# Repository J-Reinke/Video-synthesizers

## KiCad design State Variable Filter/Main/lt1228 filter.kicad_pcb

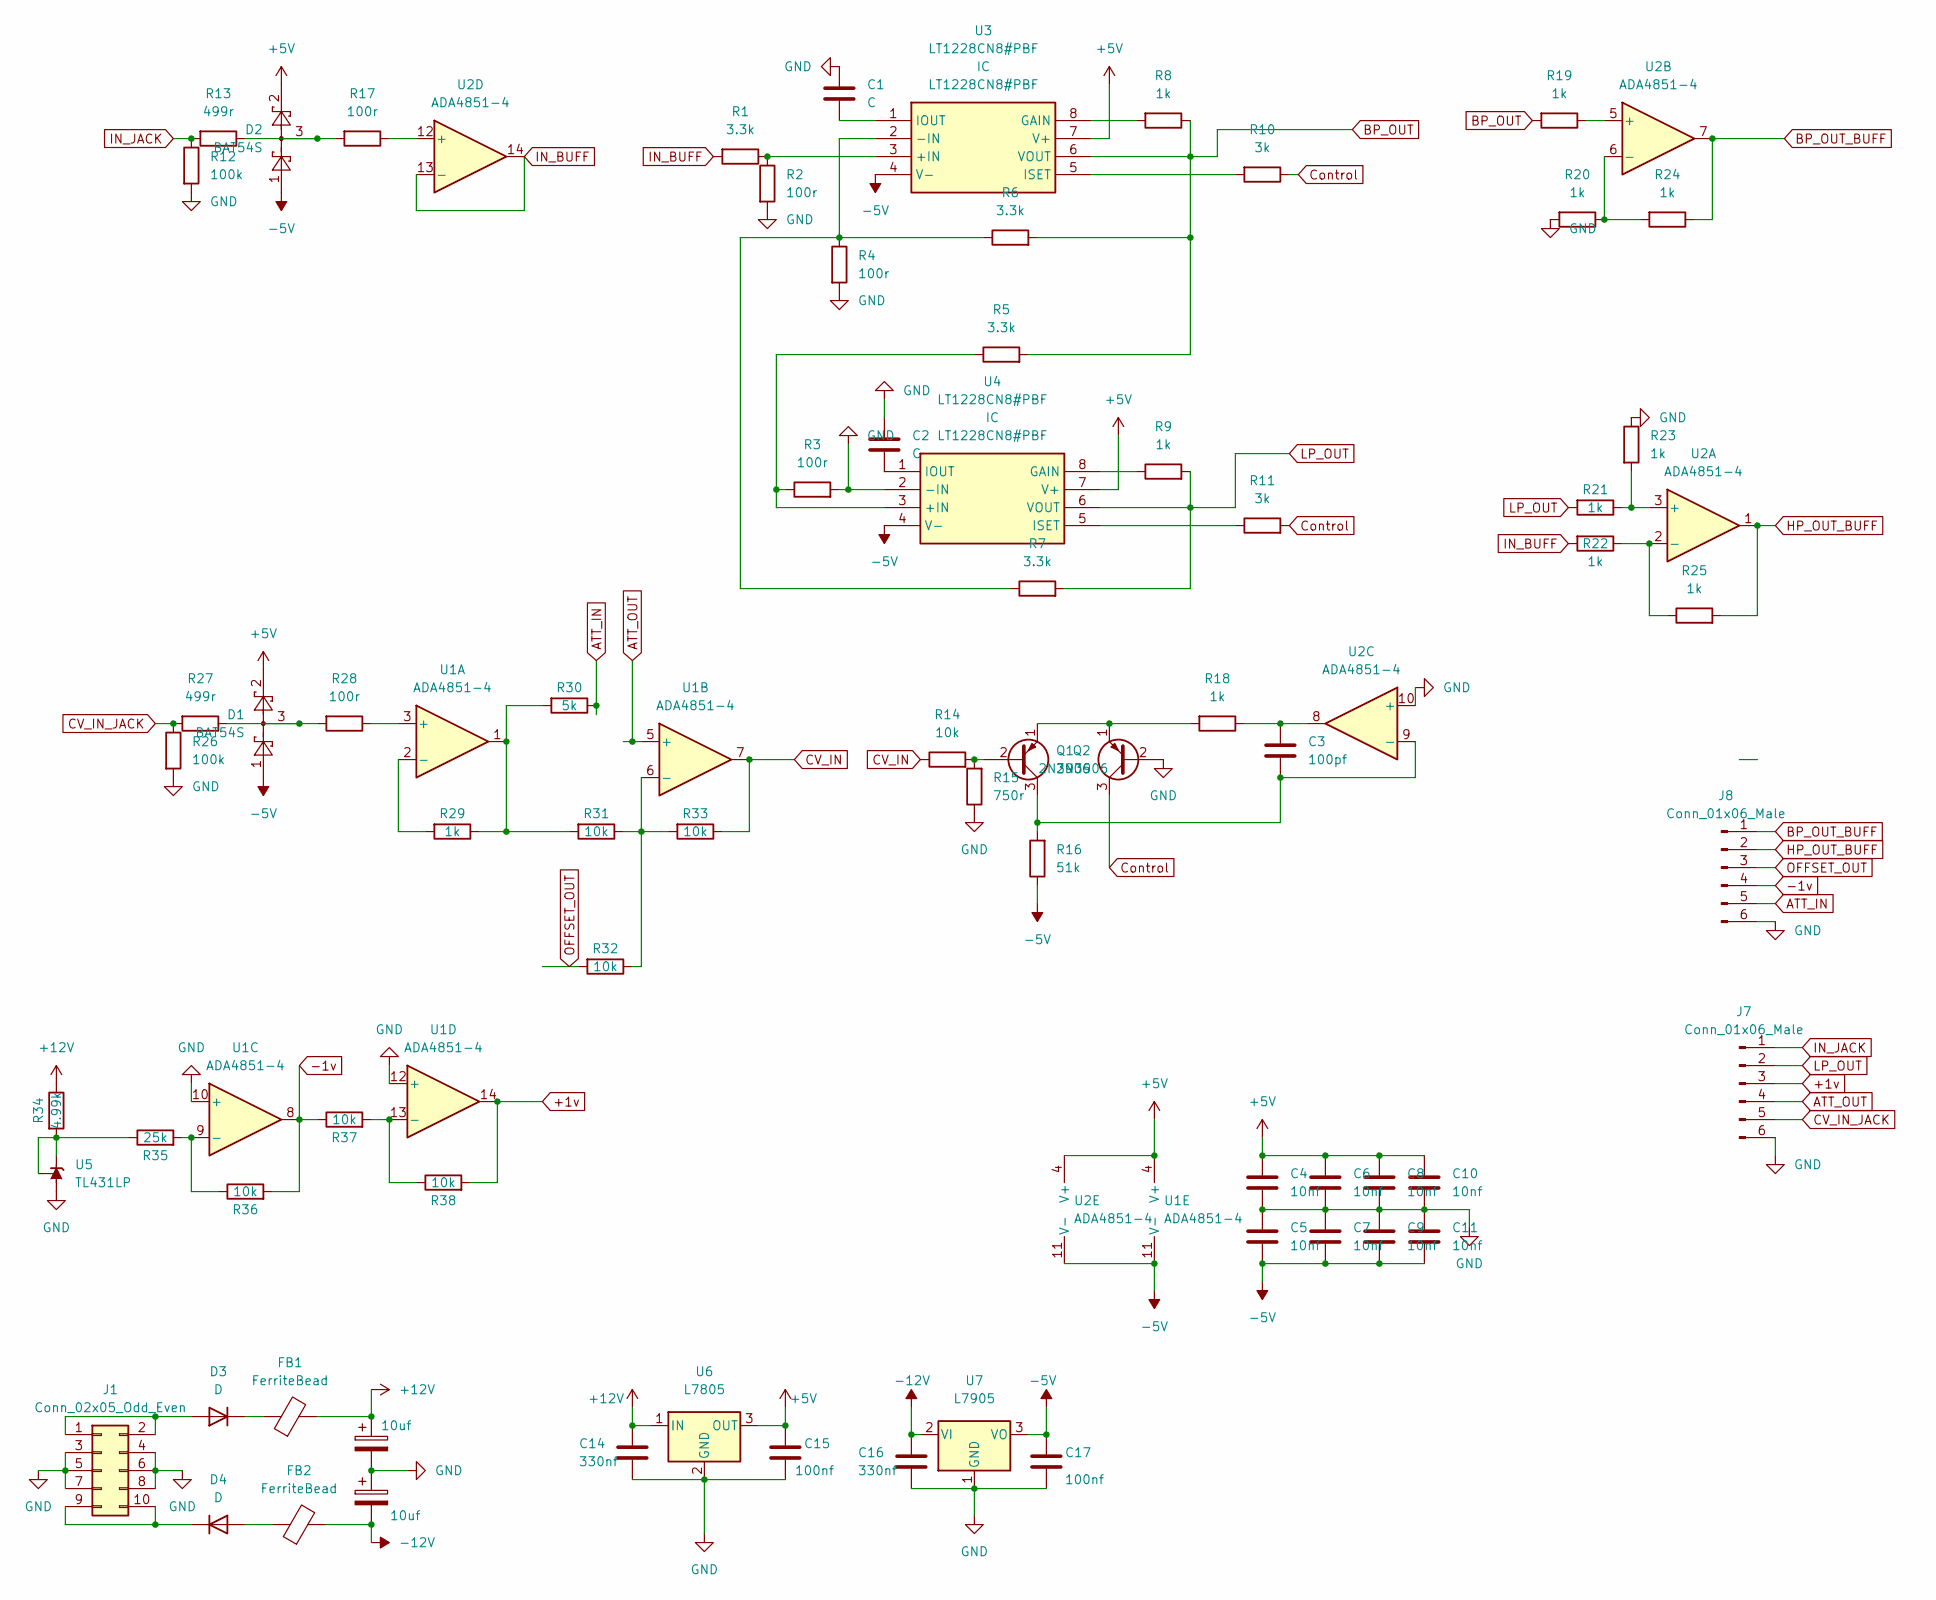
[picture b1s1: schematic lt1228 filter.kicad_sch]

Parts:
C1, C2: C; C_Disc_D3.8mm_W2.6mm_P2.50mm
C3: 100pf; C_Disc_D3.8mm_W2.6mm_P2.50mm
C4, C5, C6, C7, C8, C9, C10, C11: 10nf; C_Disc_D3.8mm_W2.6mm_P2.50mm
C12, C13: 10uf; CP_Radial_D6.3mm_P2.50mm
C14, C16: 330nf; C_Disc_D3.8mm_W2.6mm_P2.50mm
C15, C17: 100nf; C_Disc_D3.8mm_W2.6mm_P2.50mm
D1, D2: BAT54S; SOT-23
D3, D4: D; D_DO-15_P12.70mm_Horizontal
FB1, FB2: FerriteBead; R_Axial_DIN0207_L6.3mm_D2.5mm_P10.16mm_Horizontal
J1: Conn_02x05_Odd_Even; IDC-Header_2x05_P2.54mm_Vertical
J7, J8: Conn_01x06_Male; PinHeader_1x06_P2.54mm_Vertical
Q1, Q2: 2N3906; TO-92_Inline
R1, R5, R6, R7: 3.3k; R_Axial_DIN0204_L3.6mm_D1.6mm_P1.90mm_Vertical
R2, R3, R4, R17, R28: 100r; R_Axial_DIN0204_L3.6mm_D1.6mm_P1.90mm_Vertical
R8, R9, R18, R19, R20, R21, R22, R23, R24, R25, R29: 1k; R_Axial_DIN0204_L3.6mm_D1.6mm_P1.90mm_Vertical
R10, R11: 3k; R_Axial_DIN0204_L3.6mm_D1.6mm_P1.90mm_Vertical
R12, R26: 100k; R_Axial_DIN0204_L3.6mm_D1.6mm_P1.90mm_Vertical
R13, R27: 499r; R_Axial_DIN0204_L3.6mm_D1.6mm_P1.90mm_Vertical
R14, R31, R32, R33, R36, R37, R38: 10k; R_Axial_DIN0204_L3.6mm_D1.6mm_P1.90mm_Vertical
R15: 750r; R_Axial_DIN0204_L3.6mm_D1.6mm_P1.90mm_Vertical
R16: 51k; R_Axial_DIN0204_L3.6mm_D1.6mm_P1.90mm_Vertical
R30: 5k; R_Axial_DIN0204_L3.6mm_D1.6mm_P1.90mm_Vertical
R34: 4.99k; R_Axial_DIN0204_L3.6mm_D1.6mm_P1.90mm_Vertical
R35: 25k; R_Axial_DIN0204_L3.6mm_D1.6mm_P1.90mm_Vertical
U1, U2: ADA4851-4
U3, U4: LT1228CN8#PBF; DIP794W53P254L1016H394Q8N; Manufacturer_Part_Number LT1228CN8#PBF; Mouser Part Number 584-LT1228CN8#PBF
U5: TL431LP; TO-92_Inline
U6: L7805; TO-220-3_Vertical
U7: L7905; TO-220-3_Vertical

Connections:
+1v: J7.3, R38.2, U1.14
+5V: C4.1, C6.1, C8.1, C10.1, C15.1, D1.2, D2.2, U1.4 (V+), U2.4 (V+), U3.7 (V+), U4.7 (V+), U6.3 (OUT)
+12V: C12.1, C14.1, FB1.2, R34.1, U6.1 (IN)
-1v: J8.4, R36.2, R37.1, U1.8
-5V: C5.2, C7.2, C9.2, C11.2, C17.1, D1.1, D2.1, R16.1, U1.11 (V-), U2.11 (V-), U3.4 (V-), U4.4 (V-), U7.3 (VO)
-12V: C13.2, C16.1, FB2.2, U7.2 (VI)
ATT_IN: J8.5, R30.1
ATT_OUT: J7.4, U1.5 (+)
BP_OUT: R5.2, R6.2, R8.1, R19.2, U3.6 (VOUT)
BP_OUT_BUFF: J8.1, R24.1, U2.7
CV_IN: R14.1, R33.1, U1.7
CV_IN_JACK: J7.5, R26.1, R27.2
Control: Q2.3 (C), R10.1, R11.2
GND: C1.1, C2.1, C4.2, C5.1, C6.2, C7.1, C8.2, C9.1, C10.2, C11.1, C12.2, C13.1, C14.2, C15.2, C16.2, C17.2, J1.3, J1.4, J1.5, J1.6, J1.7, J1.8, J7.6, J8.6, Q2.2 (B), R2.2, R3.2, R4.2, R12.2, R15.1, R20.2, R23.1, R26.2, U1.10 (+), U1.12 (+), U2.10 (+), U4.2 (-IN), U5.2 (A), U6.2 (GND), U7.1 (GND)
HP_OUT_BUFF: J8.2, R25.2, U2.1
IN_BUFF: R1.2, R22.2, U2.13 (-), U2.14
IN_JACK: J7.1, R12.1, R13.2
LP_OUT: J7.2, R7.2, R9.2, R21.2, U4.6 (VOUT)
unnamed: C1.2, U3.1 (IOUT)
unnamed: C2.2, U4.1 (IOUT)
unnamed: C3.1, R18.1, U2.8
unnamed: C3.2, Q1.3 (C), R16.2, U2.9 (-)
unnamed: D1.3, R27.1, R28.2
unnamed: D2.3, R13.1, R17.2
unnamed: D3.1 (K), FB1.1
unnamed: D3.2 (A), J1.1, J1.2
unnamed: D4.1 (K), J1.9, J1.10
unnamed: D4.2 (A), FB2.1
unnamed: Q1.1 (E), Q2.1 (E), R18.2
unnamed: Q1.2 (B), R14.2, R15.2
unnamed: R1.1, R2.1, U3.3 (+IN)
unnamed: R3.1, R5.1, U4.3 (+IN)
unnamed: R4.1, R6.1, R7.1, U3.2 (-IN)
unnamed: R8.2, U3.8 (GAIN)
unnamed: R9.1, U4.8 (GAIN)
unnamed: R10.2, U3.5 (ISET)
unnamed: R11.1, U4.5 (ISET)
unnamed: R17.1, U2.12 (+)
unnamed: R19.1, U2.5 (+)
unnamed: R20.1, R24.2, U2.6 (-)
unnamed: R21.1, R23.2, U2.3 (+)
unnamed: R22.1, R25.1, U2.2 (-)
unnamed: R28.1, U1.3 (+)
unnamed: R29.1, R30.2, R31.2, U1.1
unnamed: R29.2, U1.2 (-)
unnamed: R31.1, R32.1, R33.2, U1.6 (-)
unnamed: R34.2, R35.1, U5.1 (REF), U5.3 (K)
unnamed: R35.2, R36.1, U1.9 (-)
unnamed: R37.2, R38.1, U1.13 (-)
OFFSET_OUT: J8.3, R32.2

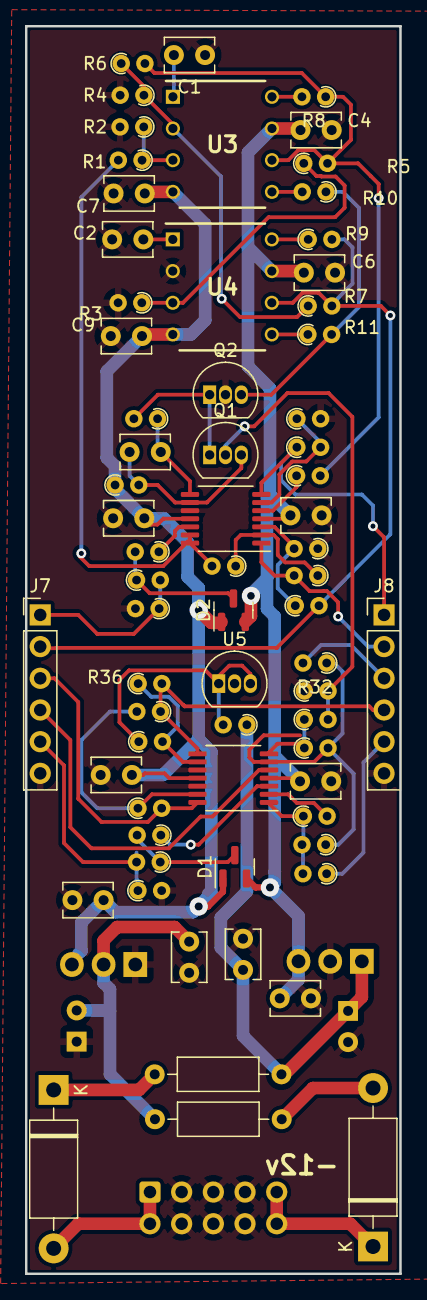
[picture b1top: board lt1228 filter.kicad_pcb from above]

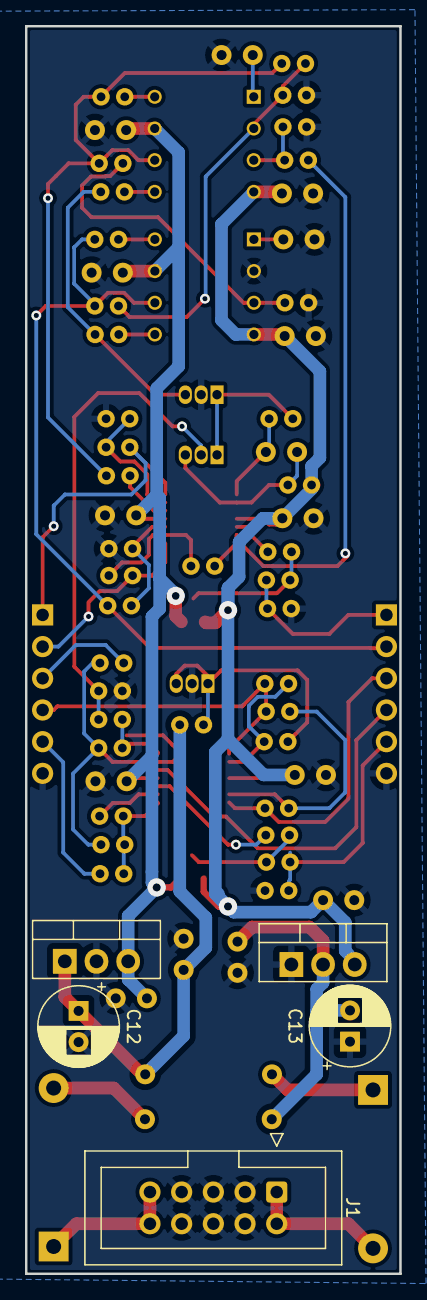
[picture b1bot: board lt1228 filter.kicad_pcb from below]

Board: 2 copper layers, 30.0 x 100.0 mm, 73 parts (5 on the bottom side), 50 nets.

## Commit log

2024-09-19 upload files
2024-10-03 update bom
